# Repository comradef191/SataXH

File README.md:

# SataXH
This is a simple breakout board that allows you to break-out the 12v & 5v rails of a SATA power connector to JSTXH connectors, allowing for easy integration of non-standard components into a PC such as an ESP-based RGB controller, which requires a 5v source but lacks a PC-compatible power input.

# NOTICE
As of 20JUl25 this board has not yet been tested, however should function.
If you wish to export your own Gerber files, please make sure to have [the Nasin Nanpa font](https://github.com/ETBCOR/nasin-nanpa) installed

## Vendors
- None... yet!

Contact me on Discord if you want to add yourself to this list!

## Bill of Materials
This BoM lists exclusively through-hole components, as SMD components will be assembled for you by JLCPCB/ect

|  Component             |QTY | Cost  |  Comment               |  Sourcing URL                                                                                                |
|------------------------|----|-------|------------------------|--------------------------------------------------------------------------------------------------------------|
|JST-XH 2-Pin            | 8  | $0.80 | Power Output           | https://www.digikey.co.uk/en/products/detail/jst-sales-america-inc/B2B-XH-A/1651045                          |
|1x2 5.08 Screw Terminal | 2  | $2.66 | Power Output           | https://www.digikey.co.uk/en/products/detail/phoenix-contact/1729128/260615                                  |
|SATA 7+15 PCB Connector | 1  | $4.09 | Power Input            | https://www.digikey.co.uk/en/products/detail/amphenol-icc-fci/10101788-002CLF/5207025                        |

## Gallery

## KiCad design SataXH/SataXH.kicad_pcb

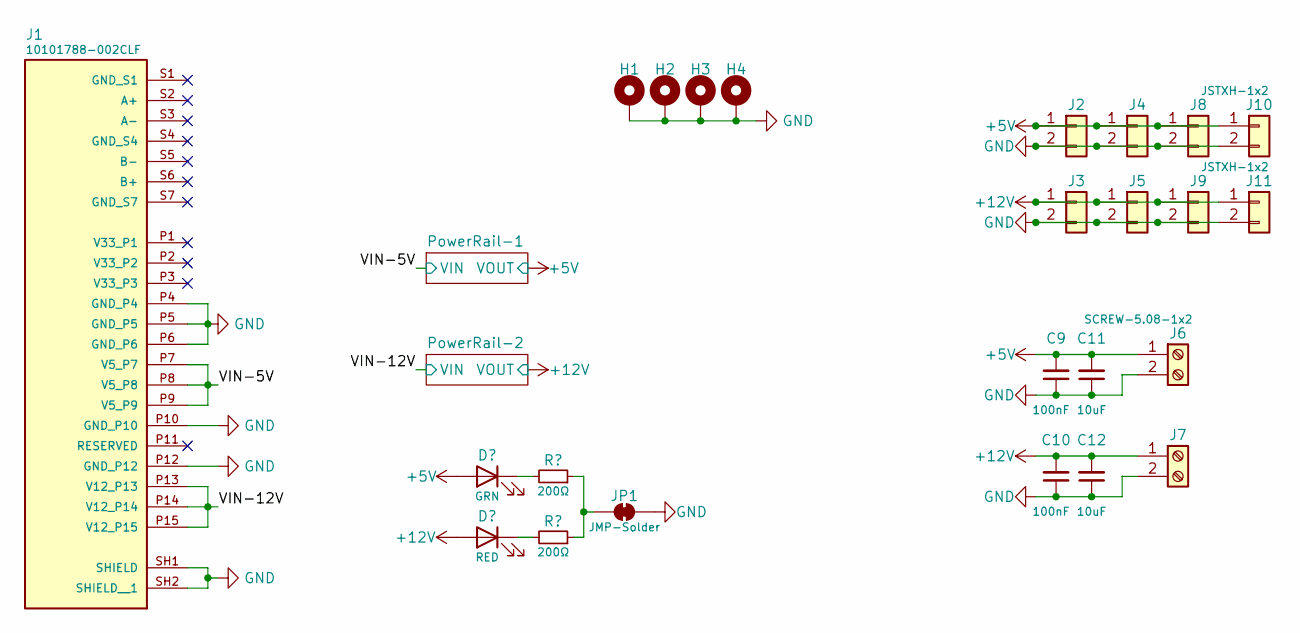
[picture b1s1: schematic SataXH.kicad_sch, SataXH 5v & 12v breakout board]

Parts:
C9, C10: 100nF; C_0402_1005Metric; LCSC C1525
C11, C12: 10uF; C_0402_1005Metric; LCSC C15525
H1, H2, H3, H4: MountingHole_Pad; M3 Mounting Hole ~ Classic - Pad
J1: 10101788-002CLF; AMPHENOL_10101788-002CLF; LCSC C254657
J2, J3, J4, J5, J8, J9, J10, J11: JSTXH-1x2; JST_XH_B2B-XH-A_1x02_P2.50mm_Vertical; LCSC C5160911
J6, J7: SCREW-5.08-1x2; TerminalBlock_Phoenix_MKDS-1,5-2-5.08_1x02_P5.08mm_Horizont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; LCSC C5188485
JP1: JMP-Solder; SolderJumper-2_P1.3mm_Bridged_Pad1.0x1.5mm

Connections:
+5V: C9.2, C11.2, J2.1, J4.1, J6.1, J8.1, J10.1; also elsewhere on the board
+12V: C10.2, C12.2, J3.1, J5.1, J7.1, J9.1, J11.1; also elsewhere on the board
/VIN-5V: J1.P7 (V5_P7), J1.P8 (V5_P8), J1.P9 (V5_P9); also elsewhere on the board
/VIN-12V: J1.P13 (V12_P13), J1.P14 (V12_P14), J1.P15 (V12_P15); also elsewhere on the board
GND: C9.1, C10.1, C11.1, C12.1, H1.1, H2.1, H3.1, H4.1, J1.P4 (GND_P4), J1.P5 (GND_P5), J1.P6 (GND_P6), J1.P10 (GND_P10), J1.P12 (GND_P12), J1.SH1 (SHIELD), J1.SH2 (SHIELD__1), J2.2, J3.2, J4.2, J5.2, J6.2, J7.2, J8.2, J9.2, J10.2, J11.2, JP1.2 (B); also elsewhere on the board
unnamed 13: JP1.1 (A); also elsewhere on the board

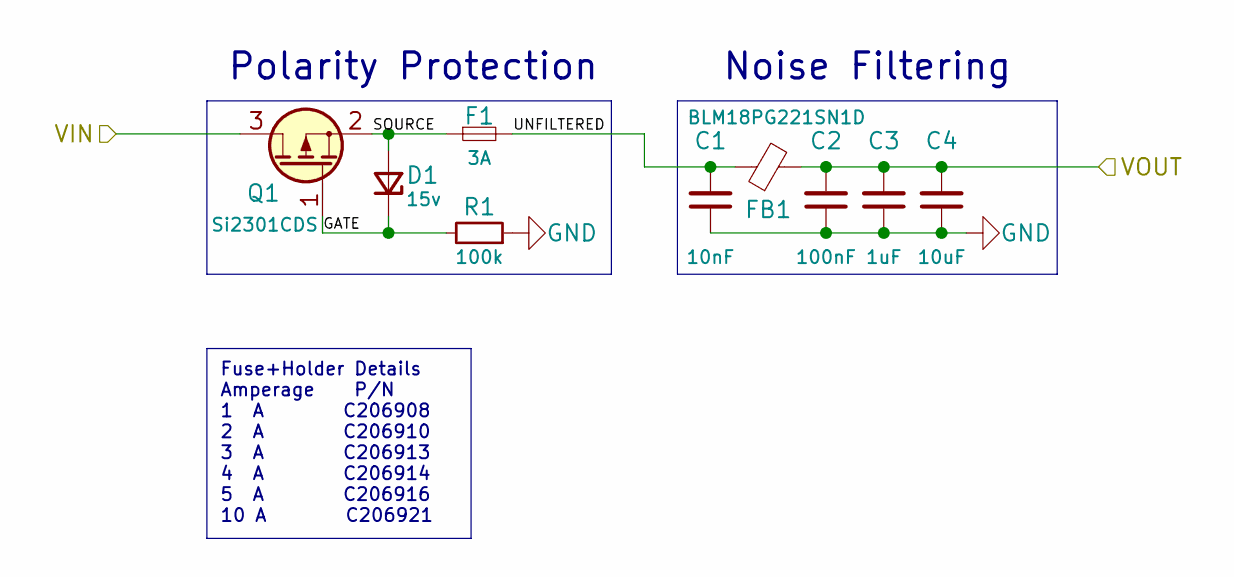
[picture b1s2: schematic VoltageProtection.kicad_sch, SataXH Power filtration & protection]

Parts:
C1: 10nF; C_0402_1005Metric; LCSC C15195
C2: 100nF; C_0402_1005Metric; LCSC C1525
C3: 1uF; C_0402_1005Metric; LCSC C52923
C4: 10uF; C_0402_1005Metric; LCSC C15525
D1: 15v; D_SOD-123; LCSC C177014
F1: 3A; Fuseholder_Littelfuse_Nano2_154x; LCSC C206913
FB1: BLM18PG221SN1D; L_0603_1608Metric; LCSC C80165
Q1: Si2301CDS; SOT-23; LCSC C10487
R1: 100k; R_0402_1005Metric; LCSC C25741

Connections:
+5V: C2.2, C3.2, C4.2, FB1.2; also elsewhere on the board
/PowerRail-1/GATE: D1.1 (K), Q1.1 (G), R1.2
/PowerRail-1/SOURCE: D1.2 (A), F1.1, Q1.2 (S)
/PowerRail-1/UNFILTERED: C1.2, F1.2, FB1.1
/VIN-5V: Q1.3 (D); also elsewhere on the board
GND: C1.1, C2.1, C3.1, C4.1, R1.1; also elsewhere on the board

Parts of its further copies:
C5: 10nF; C_0402_1005Metric; LCSC C15195
C6: 100nF; C_0402_1005Metric; LCSC C1525
C7: 1uF; C_0402_1005Metric; LCSC C52923
C8: 10uF; C_0402_1005Metric; LCSC C15525
D2: 15v; D_SOD-123; LCSC C177014
F2: 3A; Fuseholder_Littelfuse_Nano2_154x; LCSC C206913
FB2: BLM18PG221SN1D; L_0603_1608Metric; LCSC C80165
Q2: Si2301CDS; SOT-23; LCSC C10487
R2: 100k; R_0402_1005Metric; LCSC C25741

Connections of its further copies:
+12V: C6.2, C7.2, C8.2, FB2.2; also elsewhere on the board
/PowerRail-2/GATE: D2.1 (K), Q2.1 (G), R2.2
/PowerRail-2/SOURCE: D2.2 (A), F2.1, Q2.2 (S)
/PowerRail-2/UNFILTERED: C5.2, F2.2, FB2.1
/VIN-12V: Q2.3 (D); also elsewhere on the board
GND: C5.1, C6.1, C7.1, C8.1, R2.1; also elsewhere on the board

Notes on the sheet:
Noise Filtering
Polarity Protection
Fuse+Holder Details Amperage P/N 1 A C206908 2 A C206910 3 A C206913 4 A C206914 5 A C206916 10 A C206921

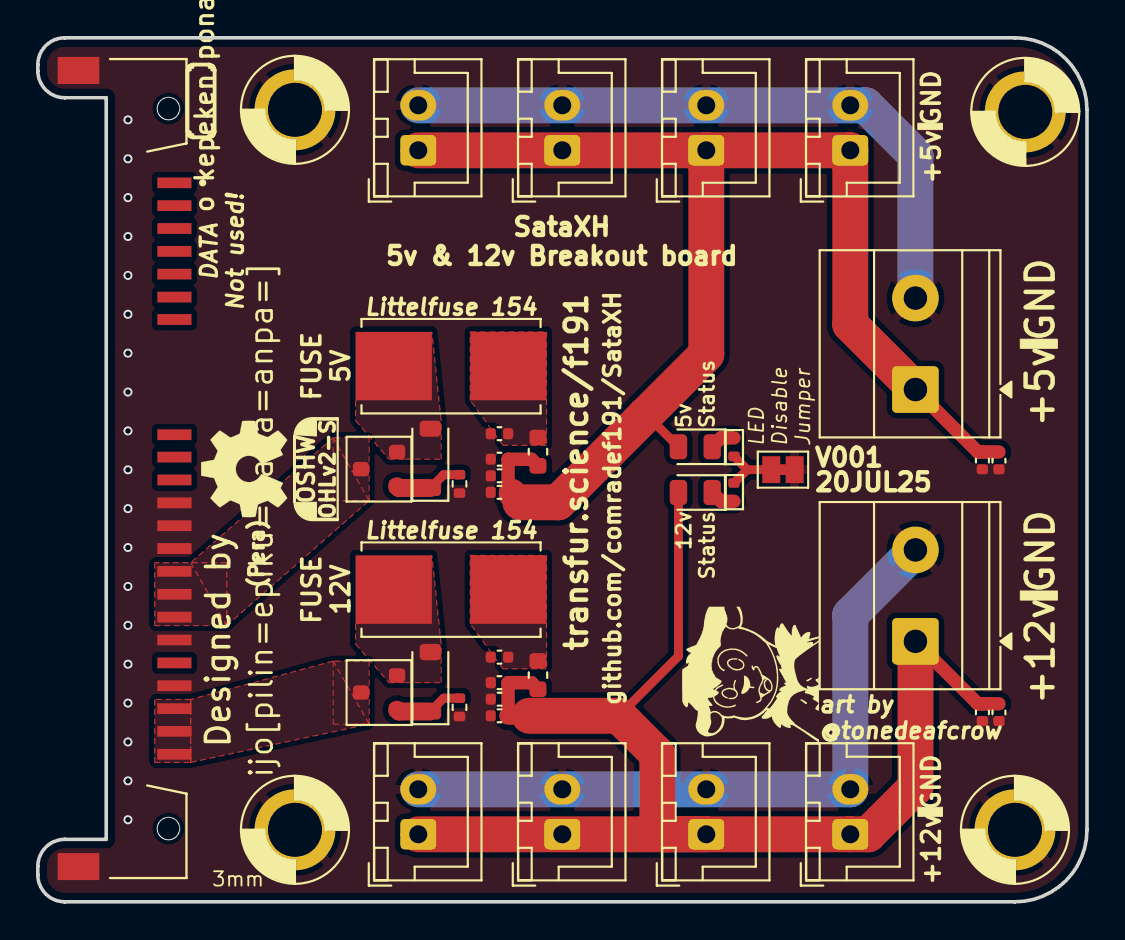
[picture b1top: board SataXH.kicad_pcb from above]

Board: 2 copper layers, 58.3 x 48.0 mm, 42 parts (0 on the bottom side), 14 nets.

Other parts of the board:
D3: GRN; LED_0805_2012Metric
D4: RED; LED_0805_2012Metric
R3, R4: 200Ω; R_0402_1005Metric

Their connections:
+5V: D3.2 (A); also elsewhere on the board
+12V: D4.2 (A); also elsewhere on the board
unnamed: D3.1 (K), R3.2
unnamed: D4.1 (K), R4.2
unnamed 13: R3.1, R4.1; also elsewhere on the board

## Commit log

2025-07-20 Add Project files
2025-07-20 Add images to ReadMe

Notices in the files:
SataXH/SataXH.kicad_sch:
CERN OHL v2 - S
